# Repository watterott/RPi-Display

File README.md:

# RPi-Display
2.8" TFT-Display (320x240) with Touchpanel for all Raspberry Pi Models.

* Open-Source and released under the [Creative Commons Attribution Share-Alike License](https://creativecommons.org/licenses/by-sa/4.0/).
* **[Documentation on learn.watterott.com](https://learn.watterott.com)**

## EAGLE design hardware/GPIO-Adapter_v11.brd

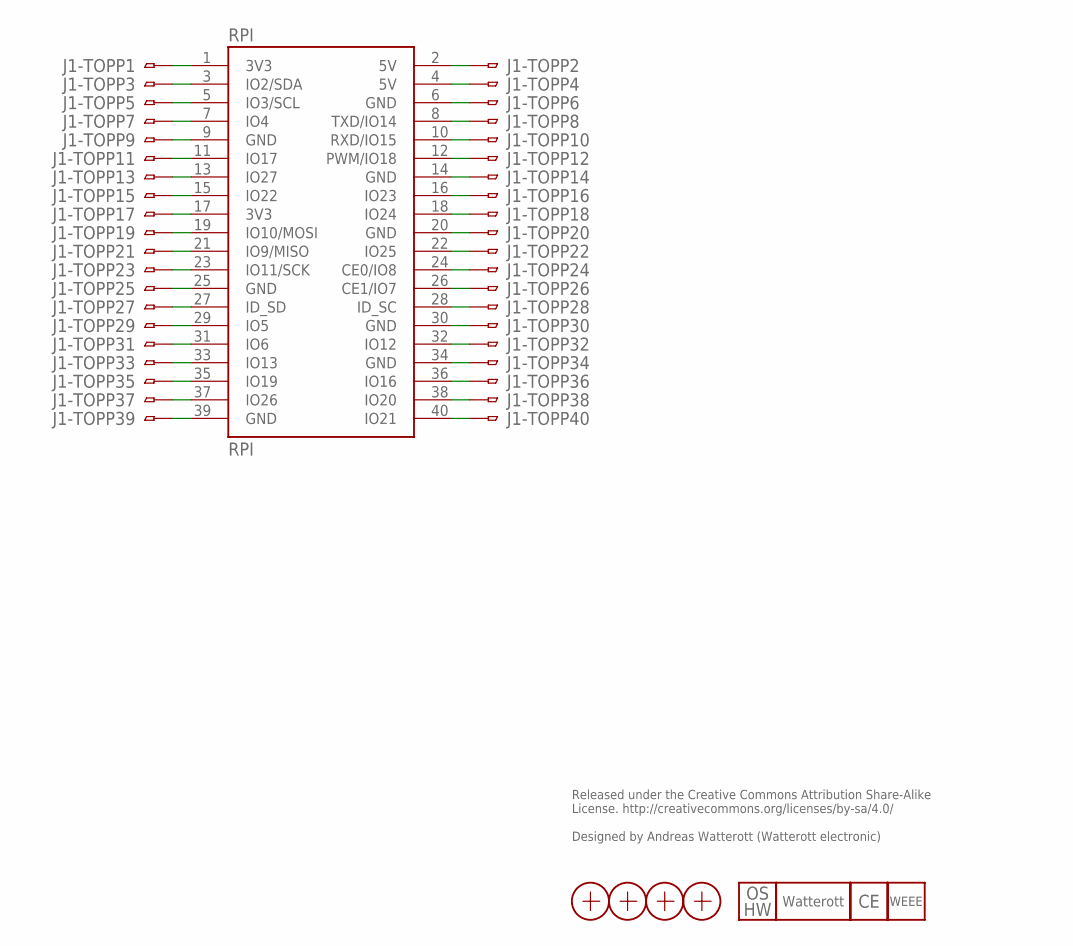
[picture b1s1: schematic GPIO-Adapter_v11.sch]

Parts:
J1-TOP: FPC40_PIN; FPC40-0.5
LOGO2: LOGO_OSHW-4; OSHW_4MM
LOGO3: LOGO_SPARK-4; SPARK_4MM
LOGO4: LOGO_CE-2; CE_2MM
LOGO5: LOGO_WEEE-4; WEEE_4MM
RPI: RPI; RPI-B+_CON_TOP
X1, X2, X3, X4: PASSER

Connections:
1: J1-TOP.1, RPI.1 (3V3)
2: J1-TOP.2, RPI.2 (5V)
3: J1-TOP.3, RPI.3 (IO2/SDA)
4: J1-TOP.4, RPI.4 (5V)
5: J1-TOP.5, RPI.5 (IO3/SCL)
6: J1-TOP.6, RPI.6 (GND)
7: J1-TOP.7, RPI.7 (IO4)
8: J1-TOP.8, RPI.8 (TXD/IO14)
9: J1-TOP.9, RPI.9 (GND)
10: J1-TOP.10, RPI.10 (RXD/IO15)
11: J1-TOP.11, RPI.11 (IO17)
12: J1-TOP.12, RPI.12 (PWM/IO18)
13: J1-TOP.13, RPI.13 (IO27)
14: J1-TOP.14, RPI.14 (GND)
15: J1-TOP.15, RPI.15 (IO22)
16: J1-TOP.16, RPI.16 (IO23)
17: J1-TOP.17, RPI.17 (3V3)
18: J1-TOP.18, RPI.18 (IO24)
19: J1-TOP.19, RPI.19 (IO10/MOSI)
20: J1-TOP.20, RPI.20 (GND)
21: J1-TOP.21, RPI.21 (IO9/MISO)
22: J1-TOP.22, RPI.22 (IO25)
23: J1-TOP.23, RPI.23 (IO11/SCK)
24: J1-TOP.24, RPI.24 (CE0/IO8)
25: J1-TOP.25, RPI.25 (GND)
26: J1-TOP.26, RPI.26 (CE1/IO7)
27: J1-TOP.27, RPI.27 (ID_SD)
28: J1-TOP.28, RPI.28 (ID_SC)
29: J1-TOP.29, RPI.29 (IO5)
30: J1-TOP.30, RPI.30 (GND)
31: J1-TOP.31, RPI.31 (IO6)
32: J1-TOP.32, RPI.32 (IO12)
33: J1-TOP.33, RPI.33 (IO13)
34: J1-TOP.34, RPI.34 (GND)
35: J1-TOP.35, RPI.35 (IO19)
36: J1-TOP.36, RPI.36 (IO16)
37: J1-TOP.37, RPI.37 (IO26)
38: J1-TOP.38, RPI.38 (IO20)
39: J1-TOP.39, RPI.39 (GND)
40: J1-TOP.40, RPI.40 (IO21)

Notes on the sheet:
Released under the Creative Commons Attribution Share-Alike License. http://creativecommons.org/licenses/by-sa/4.0/ Designed by Andreas Watterott (Watterott electronic)

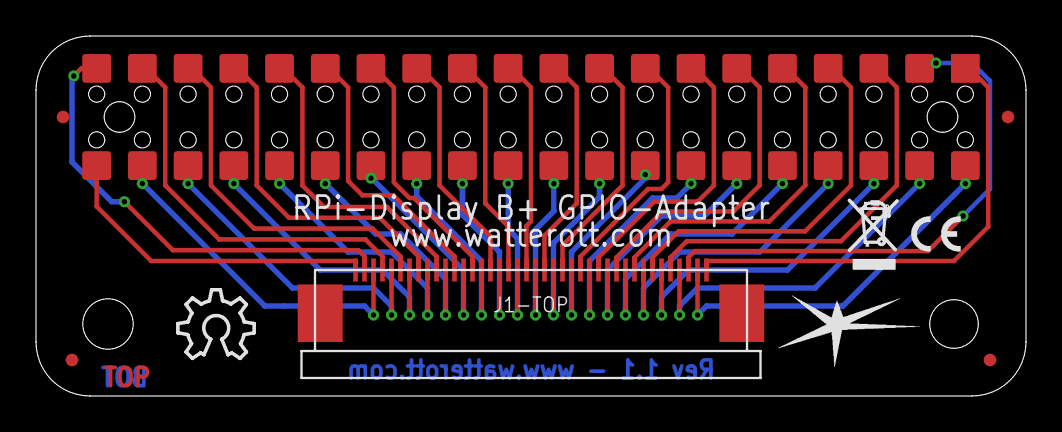
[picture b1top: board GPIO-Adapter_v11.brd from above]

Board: 2 copper layers, 55.0 x 20.0 mm, 10 parts (0 on the bottom side), 40 nets.

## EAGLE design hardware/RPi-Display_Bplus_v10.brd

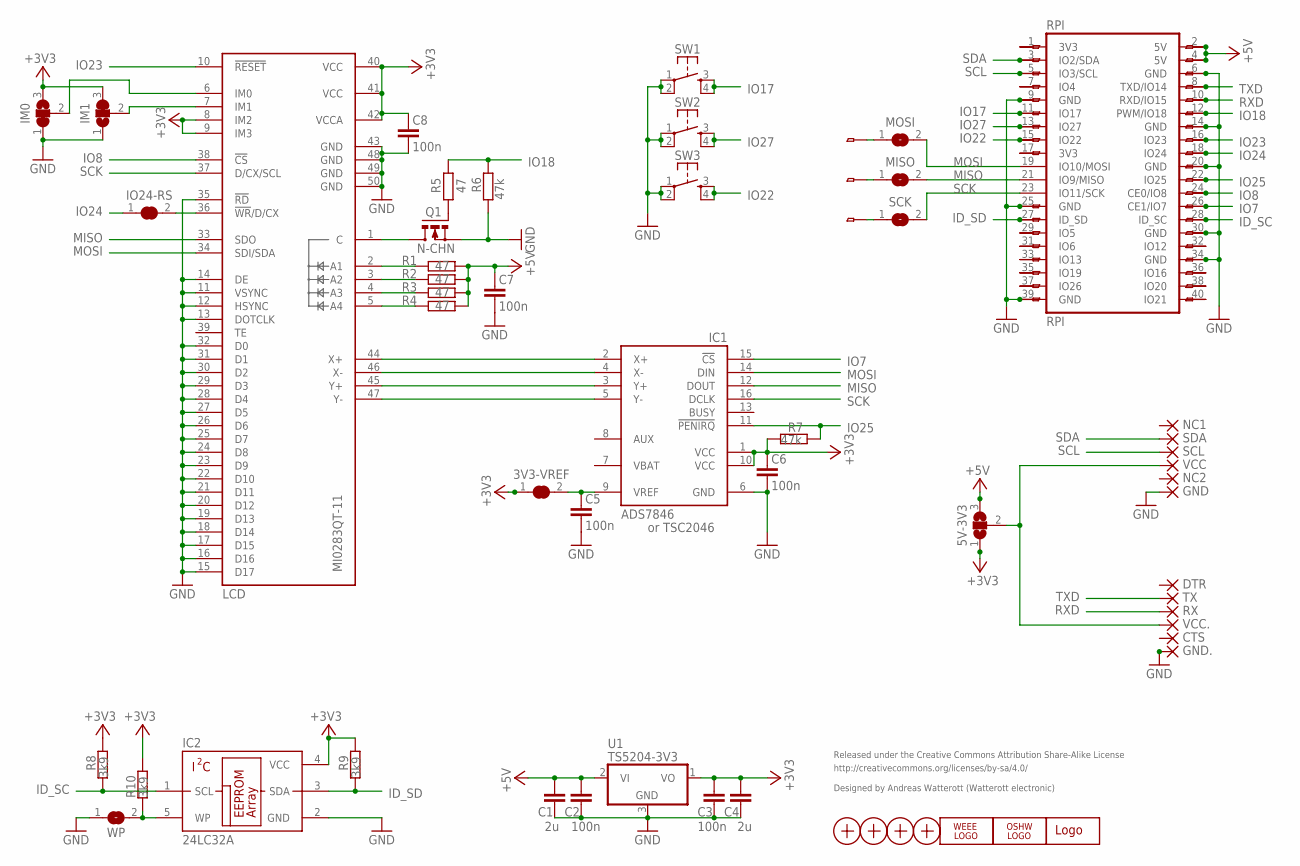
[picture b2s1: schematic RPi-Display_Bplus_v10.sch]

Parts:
3V3-VREF: JUMPER2-NOCREAM; JUMPER2_NC
5V-3V3: JUMPER3-NOCREAM; JUMPER3_NC
C1, C4: 2u; C0603
C2, C3, C5, C6, C7, C8: 100n; C0603
CTS: PAD-1.27-NC; PAD-1.27X2.54_NC
DTR: PAD-1.27-NC; PAD-1.27X2.54_NC
GND, GND.: PAD-1.27-NC; PAD-1.27X2.54_NC
GPIO: FH12-40S-0.5SH
IC1: ADS7846; SSOP16
IC2: 24LC32A; SOT23-5
IM0, IM1: JUMPER3-NOCREAM; JUMPER3_NC
IO24-RS: JUMPER2-NOCREAM; JUMPER2_NC
LCD: MI0283QT-11; MI0283QT11
LOGO1: OSHW_LOGO_6MILX0150-NT; OSHW_6X150_NOTEXT
LOGO2: WEEE_LOGO; WEEE
MISO: JUMPER2-NOCREAM; JUMPER2_NC
MOSI: JUMPER2-NOCREAM; JUMPER2_NC
NC1, NC2: PAD-1.27-NC; PAD-1.27X2.54_NC
Q1: N-CHN; MICRO3
R1, R2, R3, R4, R5: 47; R0603
R6, R7: 47k; R0603
R8, R9, R10: 3k9; R0603
RPI: RPI; RPI_B+
RX: PAD-1.27-NC; PAD-1.27X2.54_NC
SCK: JUMPER2-NOCREAM; JUMPER2_NC
SCL: PAD-1.27-NC; PAD-1.27X2.54_NC
SDA: PAD-1.27-NC; PAD-1.27X2.54_NC
SW1, SW2, SW3: SWITCH-PTS840P; SW_PTS840P
TX: PAD-1.27-NC; PAD-1.27X2.54_NC
U1: TS5204-3V3; SOT23
U$1: WE-LOGO
VCC, VCC.: PAD-1.27-NC; PAD-1.27X2.54_NC
WP: JUMPER2-NOCREAM; JUMPER2_NC
X1, X2, X3, X4: PASSER

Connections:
+3V3: 3V3-VREF.1, 5V-3V3.1, C3.1, C4.1, C6.1, C8.1, IC1.1 (VCC), IC1.10 (VCC), IC2.4 (VCC), IM0.3, IM1.3, LCD.8 (IM2), LCD.9 (IM3), LCD.40 (VCC), LCD.41 (VCC), LCD.42 (VCCA), R7.2, R8.1, R9.1, R10.1, U1.1 (VO)
+5V: 5V-3V3.3, C1.1, C2.1, C7.1, GPIO.37, GPIO.39, R1.2, R2.2, R3.2, R4.2, RPI.2 (5V), RPI.4 (5V), U1.2 (VI)
C1: LCD.1 (C), Q1.3 (D)
GND: C1.2, C2.2, C3.2, C4.2, C5.2, C6.2, C7.2, C8.2, GND.1, GND..1, GPIO.2, GPIO.7, GPIO.11, GPIO.16, GPIO.21, GPIO.27, GPIO.32, GPIO.35, IC1.6 (GND), IC2.2 (GND), IM0.1, IM1.1, LCD.11 (VSYNC), LCD.12 (HSYNC), LCD.13 (DOTCLK), LCD.14 (DE), LCD.15 (D17), LCD.16 (D16), LCD.17 (D15), LCD.18 (D14), LCD.19 (D13), LCD.20 (D12), LCD.21 (D11), LCD.22 (D10), LCD.23 (D9), LCD.24 (D8), LCD.25 (D7), LCD.26 (D6), LCD.27 (D5), LCD.28 (D4), LCD.29 (D3), LCD.30 (D2), LCD.31 (D1), LCD.32 (D0), LCD.35 (!RD), LCD.43 (GND), LCD.48 (GND), LCD.49 (GND), LCD.50 (GND), Q1.2 (S), R6.2, RPI.6 (GND), RPI.9 (GND), RPI.14 (GND), RPI.20 (GND), RPI.25 (GND), RPI.30 (GND), RPI.34 (GND), RPI.39 (GND), SW1.1, SW1.2 (P1), SW2.1, SW2.2 (P1), SW3.1, SW3.2 (P1), U1.3 (GND), WP.1
ID_SC: GPIO.13, IC2.1 (SCL), R8.2, RPI.28 (ID_SC)
ID_SD: GPIO.14, IC2.3 (SDA), R9.2, RPI.27 (ID_SD)
IM0: IM0.2, LCD.6 (IM0)
IM1: IM1.2, LCD.7 (IM1)
IO7: GPIO.15, IC1.15 (!CS), RPI.26 (CE1/IO7)
IO8: GPIO.17, LCD.38 (!CS), RPI.24 (CE0/IO8)
IO17: GPIO.30, RPI.11 (IO17), SW1.3 (S), SW1.4 (S1)
IO18: GPIO.29, R5.2, R6.1, RPI.12 (PWM/IO18)
IO22: GPIO.26, RPI.15 (IO22), SW3.3 (S), SW3.4 (S1)
IO23: GPIO.25, LCD.10 (!RESET), RPI.16 (IO23)
IO24: GPIO.23, IO24-RS.1, RPI.18 (IO24)
IO25: GPIO.19, IC1.11 (!PENIRQ), R7.1, RPI.22 (IO25)
IO27: GPIO.28, RPI.13 (IO27), SW2.3 (S), SW2.4 (S1)
LEDPWM: Q1.1 (G), R5.1
LED_A1: LCD.2 (A1), R1.1
LED_A2: LCD.3 (A2), R2.1
LED_A3: LCD.4 (A3), R3.1
LED_A4: LCD.5 (A4), R4.1
MISO: IC1.12 (DOUT), LCD.33 (SDO), MISO.2, RPI.21 (IO9/MISO)
MOSI: IC1.14 (DIN), LCD.34 (SDI/SDA), MOSI.2, RPI.19 (IO10/MOSI)
unnamed: IO24-RS.2, LCD.36 (!WR!/D/CX)
unnamed: IC2.5 (WP), R10.2, WP.2
unnamed: GPIO.22, MOSI.1
unnamed: 5V-3V3.2, VCC.1, VCC..1
unnamed: GPIO.20, MISO.1
unnamed: GPIO.18, SCK.1
unnamed: GPIO.40, RPI.1 (3V3)
unnamed: GPIO.34, RPI.7 (IO4)
unnamed: GPIO.24, RPI.17 (3V3)
unnamed: GPIO.12, RPI.29 (IO5)
unnamed: GPIO.10, RPI.31 (IO6)
unnamed: GPIO.8, RPI.33 (IO13)
unnamed: GPIO.6, RPI.35 (IO19)
unnamed: GPIO.4, RPI.37 (IO26)
unnamed: GPIO.9, RPI.32 (IO12)
unnamed: GPIO.5, RPI.36 (IO16)
unnamed: GPIO.3, RPI.38 (IO20)
unnamed: GPIO.1, RPI.40 (IO21)
RXD: GPIO.31, RPI.10 (RXD/IO15), RX.1
SCK: IC1.16 (DCLK), LCD.37 (D/CX/SCL), RPI.23 (IO11/SCK), SCK.2
SCL: GPIO.36, RPI.5 (IO3/SCL), SCL.1
SDA: GPIO.38, RPI.3 (IO2/SDA), SDA.1
TXD: GPIO.33, RPI.8 (TXD/IO14), TX.1
VREF: 3V3-VREF.2, C5.1, IC1.9 (VREF)
X+: IC1.2 (X+), LCD.44 (X+)
X-: IC1.4 (X-), LCD.46 (X-)
Y+: IC1.3 (Y+), LCD.45 (Y+)
Y-: IC1.5 (Y-), LCD.47 (Y-)

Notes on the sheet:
Released under the Creative Commons Attribution Share-Alike License
http://creativecommons.org/licenses/by-sa/4.0/
Designed by Andreas Watterott (Watterott electronic)
or TSC2046

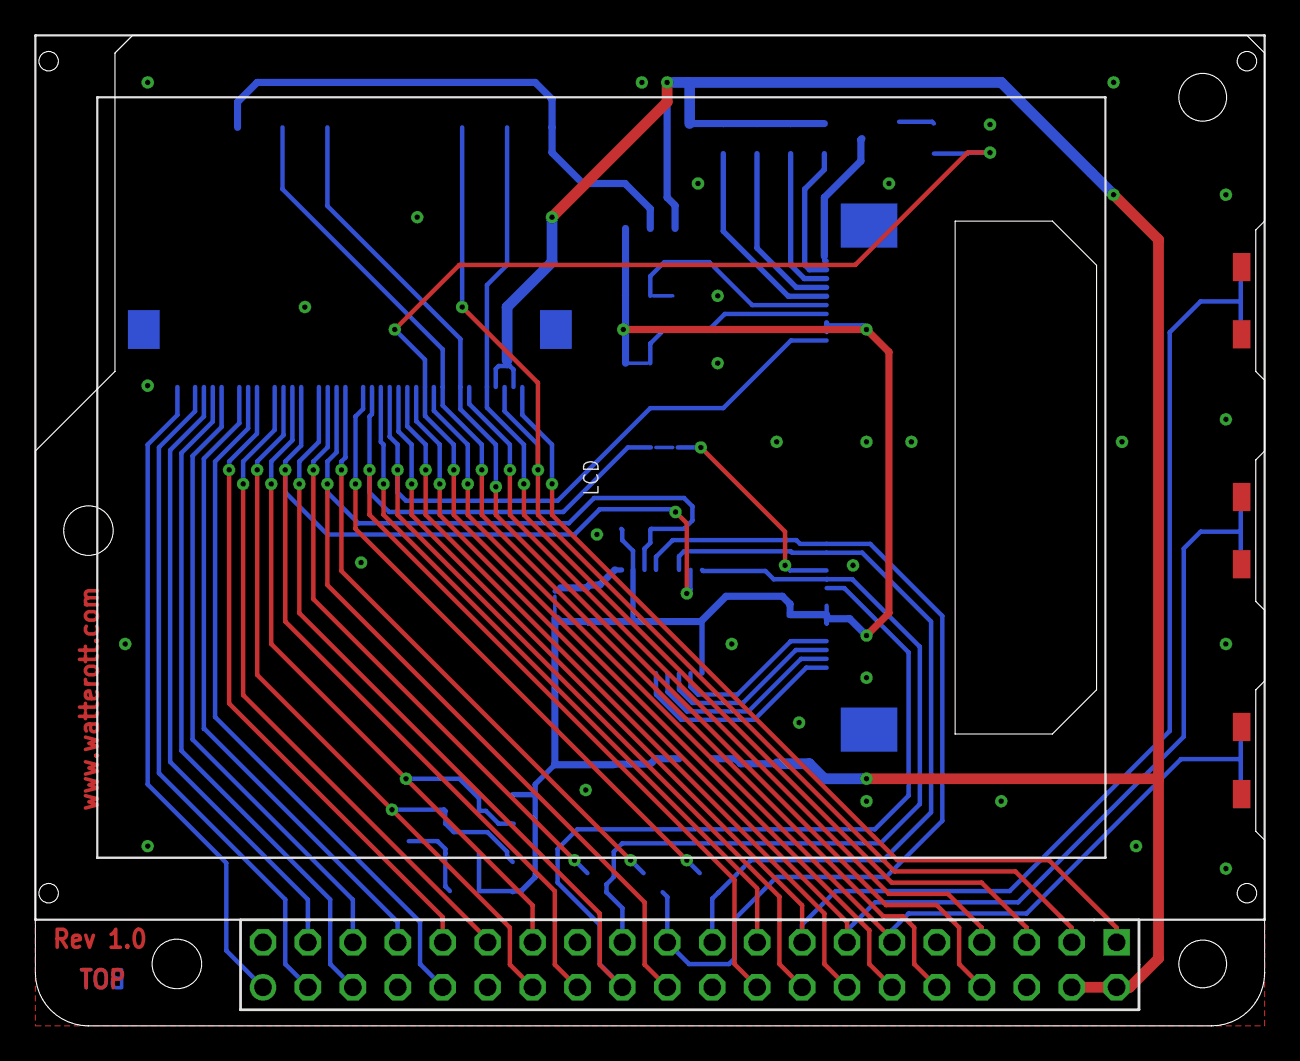
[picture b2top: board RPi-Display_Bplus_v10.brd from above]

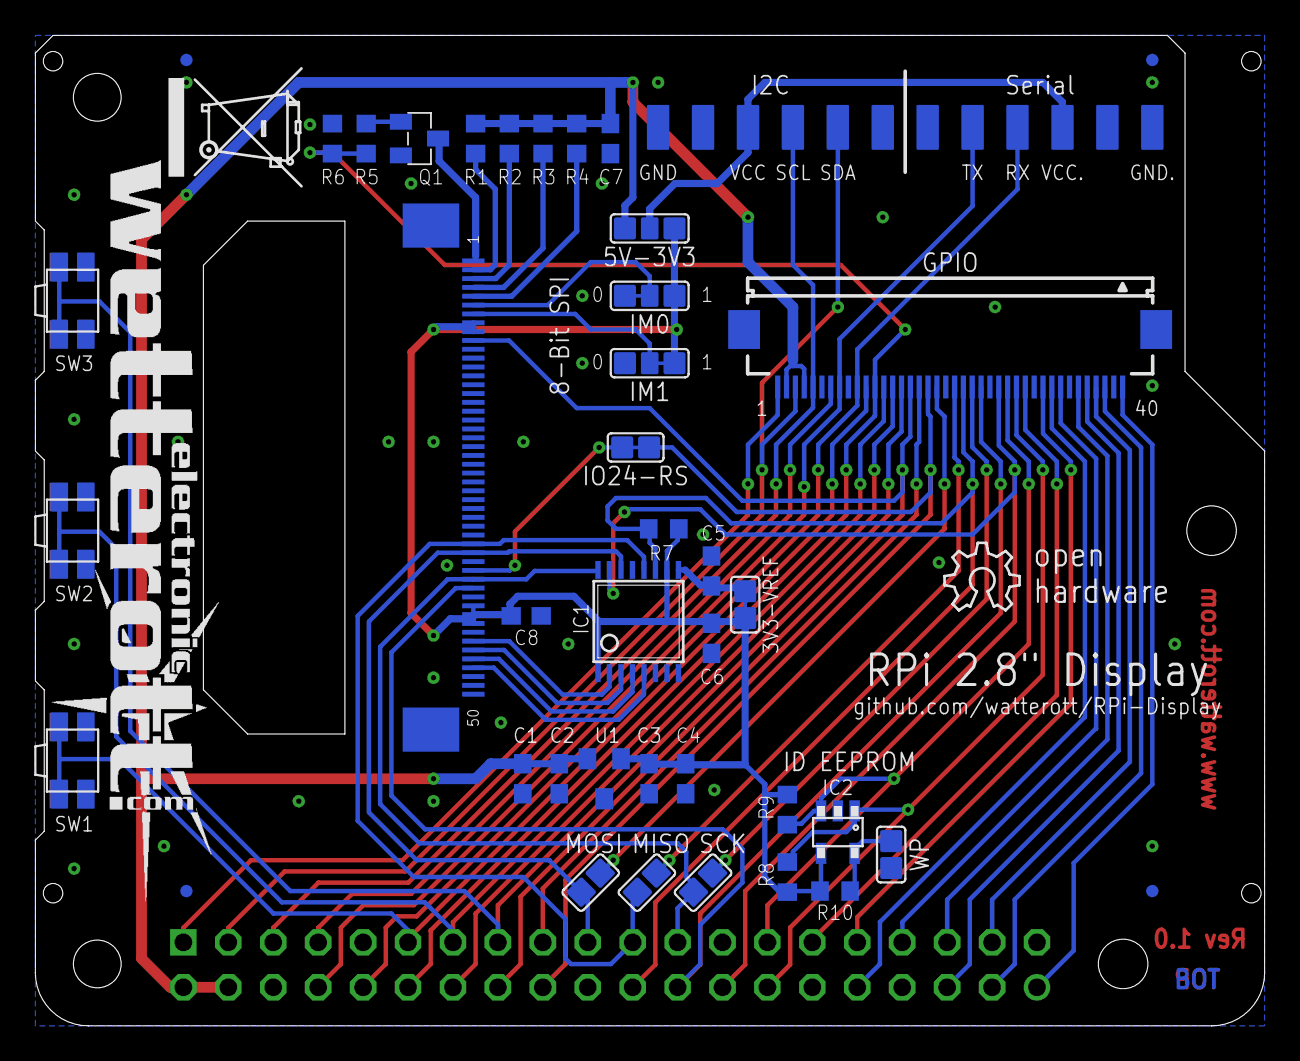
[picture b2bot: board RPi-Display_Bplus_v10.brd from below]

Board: 2 copper layers, 69.5 x 56.0 mm, 56 parts (54 on the bottom side), 52 nets.

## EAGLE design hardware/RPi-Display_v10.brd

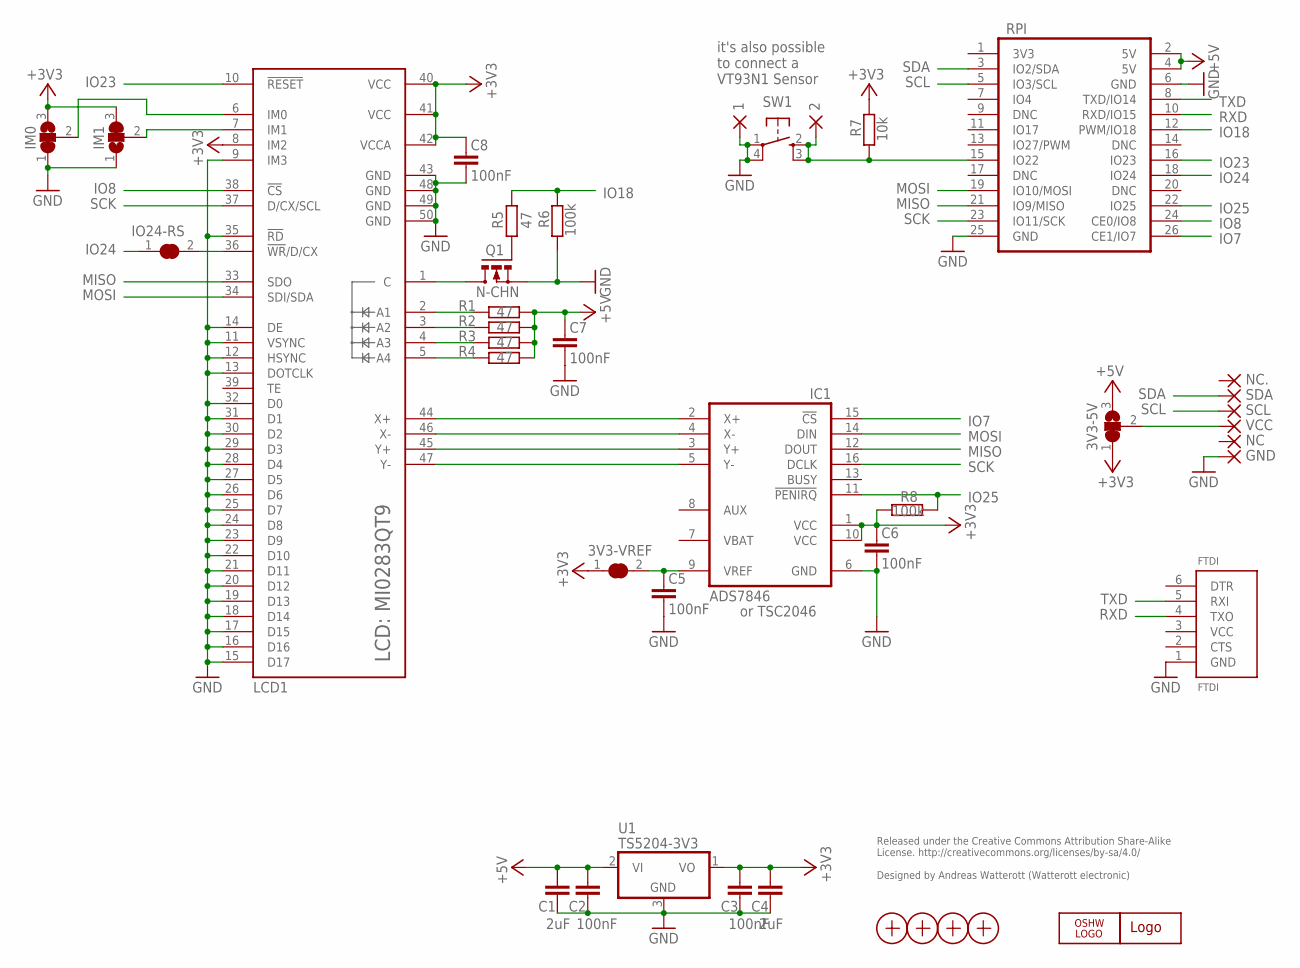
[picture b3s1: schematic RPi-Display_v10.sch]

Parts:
1, 2: WIREPADSMD1,27-254; SMD1,27-2,54
3V3-5V: SJ2W; SJ_2
3V3-VREF: SJ
C1, C4: 2uF; C0603
C2, C3, C5, C6, C7, C8: 100nF; C0603
FTDI: FTDI
GND: WIREPADSMD1,27-254; SMD1,27-2,54
IC1: ADS7846; SSOP16
IM0, IM1: SJ2W; SJ_2
IO24-RS: SJ
LCD1: MI0283QT9
LOGO1: OSHW_LOGO_6MILX0150-NT; OSHW_6X150_NOTEXT
NC, NC.: WIREPADSMD1,27-254; SMD1,27-2,54
Q1: N-CHN; MICRO3
R1, R2, R3, R4, R5: 47; R0603
R6, R8: 100k; R0603
R7: 10k; R0603
RPI: RPI
SCL: WIREPADSMD1,27-254; SMD1,27-2,54
SDA: WIREPADSMD1,27-254; SMD1,27-2,54
SW1: SW4S; SW_SMD4
U1: TS5204-3V3; SOT23
U$1: WE-LOGO
VCC: WIREPADSMD1,27-254; SMD1,27-2,54
X1, X2, X3, X4: PASSER

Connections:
+3V3: 3V3-5V.1, 3V3-VREF.1, C3.1, C4.1, C6.1, C8.1, IC1.1 (VCC), IC1.10 (VCC), IM0.3, IM1.3, LCD1.8 (IM2), LCD1.40 (VCC), LCD1.41 (VCC), LCD1.42 (VCCA), R7.1, R8.2, U1.1 (VO)
+5V: 3V3-5V.3, C1.1, C2.1, C7.1, R1.2, R2.2, R3.2, R4.2, RPI.2 (5V), RPI.4 (5V), U1.2 (VI)
C1: LCD1.1 (C), Q1.3 (D)
GND: 1.1, C1.2, C2.2, C3.2, C4.2, C5.2, C6.2, C7.2, C8.2, FTDI.1 (GND), GND.1, IC1.6 (GND), IM0.1, IM1.1, LCD1.9 (IM3), LCD1.11 (VSYNC), LCD1.12 (HSYNC), LCD1.13 (DOTCLK), LCD1.14 (DE), LCD1.15 (D17), LCD1.16 (D16), LCD1.17 (D15), LCD1.18 (D14), LCD1.19 (D13), LCD1.20 (D12), LCD1.21 (D11), LCD1.22 (D10), LCD1.23 (D9), LCD1.24 (D8), LCD1.25 (D7), LCD1.26 (D6), LCD1.27 (D5), LCD1.28 (D4), LCD1.29 (D3), LCD1.30 (D2), LCD1.31 (D1), LCD1.32 (D0), LCD1.35 (!RD), LCD1.43 (GND), LCD1.48 (GND), LCD1.49 (GND), LCD1.50 (GND), Q1.2 (S), R6.2, RPI.6 (GND), RPI.25 (GND), SW1.1, SW1.4 (P1), U1.3 (GND)
IM0: IM0.2, LCD1.6 (IM0)
IM1: IM1.2, LCD1.7 (IM1)
IO7: IC1.15 (!CS), RPI.26 (CE1/IO7)
IO8: LCD1.38 (!CS), RPI.24 (CE0/IO8)
IO18: R5.2, R6.1, RPI.12 (PWM/IO18)
IO22: 2.1, R7.2, RPI.15 (IO22), SW1.2 (S), SW1.3 (S1)
IO23: LCD1.10 (!RESET), RPI.16 (IO23)
IO24: IO24-RS.1, RPI.18 (IO24)
IO25: IC1.11 (!PENIRQ), R8.1, RPI.22 (IO25)
LEDPWM: Q1.1 (G), R5.1
LED_A1: LCD1.2 (A1), R1.1
LED_A2: LCD1.3 (A2), R2.1
LED_A3: LCD1.4 (A3), R3.1
LED_A4: LCD1.5 (A4), R4.1
MISO: IC1.12 (DOUT), LCD1.33 (SDO), RPI.21 (IO9/MISO)
MOSI: IC1.14 (DIN), LCD1.34 (SDI/SDA), RPI.19 (IO10/MOSI)
unnamed: IO24-RS.2, LCD1.36 (!WR!/D/CX)
unnamed: 3V3-5V.2, VCC.1
RXD: FTDI.4 (TXO), RPI.10 (RXD/IO15)
SCK: IC1.16 (DCLK), LCD1.37 (D/CX/SCL), RPI.23 (IO11/SCK)
SCL: RPI.5 (IO3/SCL), SCL.1
SDA: RPI.3 (IO2/SDA), SDA.1
TXD: FTDI.5 (RXI), RPI.8 (TXD/IO14)
VREF: 3V3-VREF.2, C5.1, IC1.9 (VREF)
X+: IC1.2 (X+), LCD1.44 (X+)
X-: IC1.4 (X-), LCD1.46 (X-)
Y+: IC1.3 (Y+), LCD1.45 (Y+)
Y-: IC1.5 (Y-), LCD1.47 (Y-)

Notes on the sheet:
Released under the Creative Commons Attribution Share-Alike License. http://creativecommons.org/licenses/by-sa/4.0/ Designed by Andreas Watterott (Watterott electronic)
or TSC2046
it's also possible to connect a VT93N1 Sensor

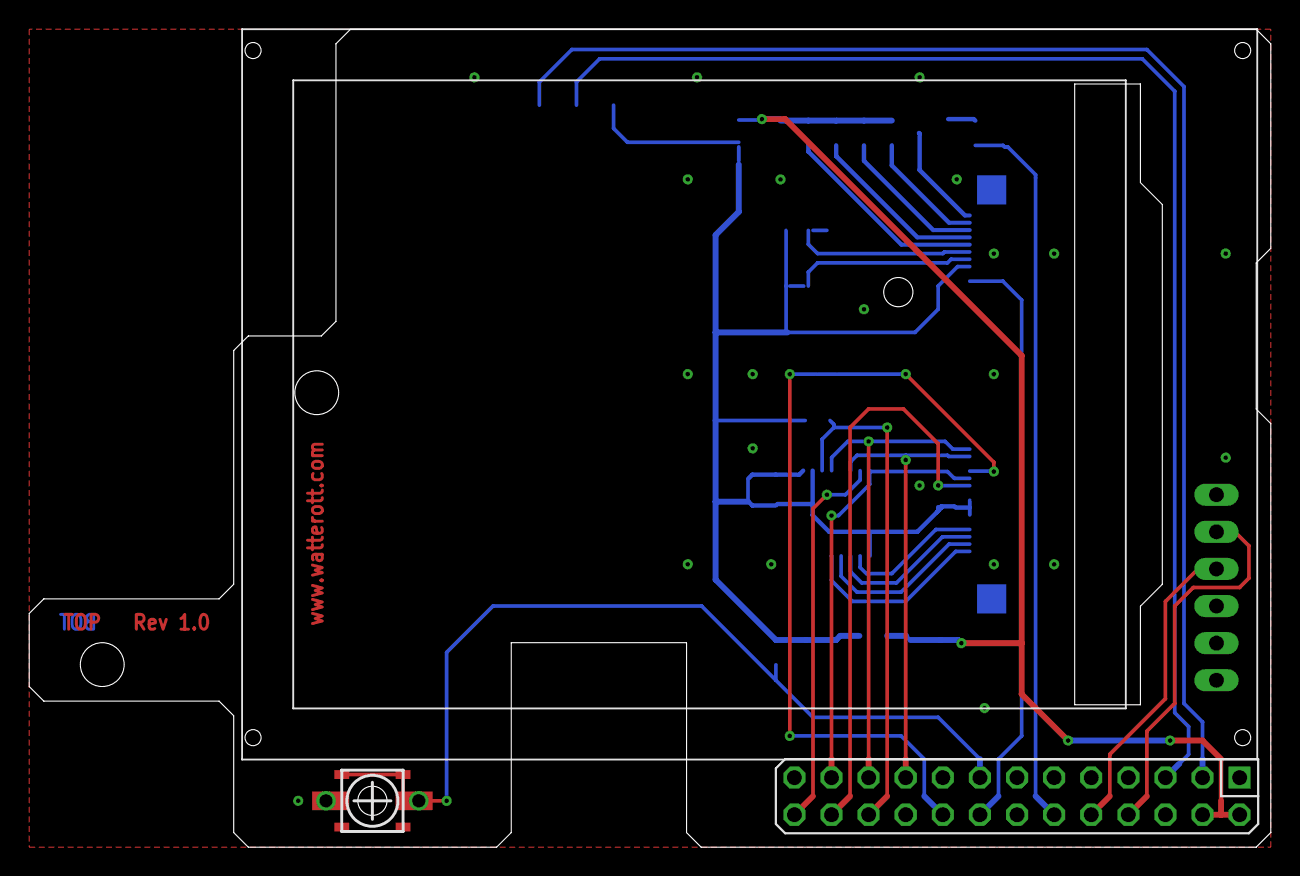
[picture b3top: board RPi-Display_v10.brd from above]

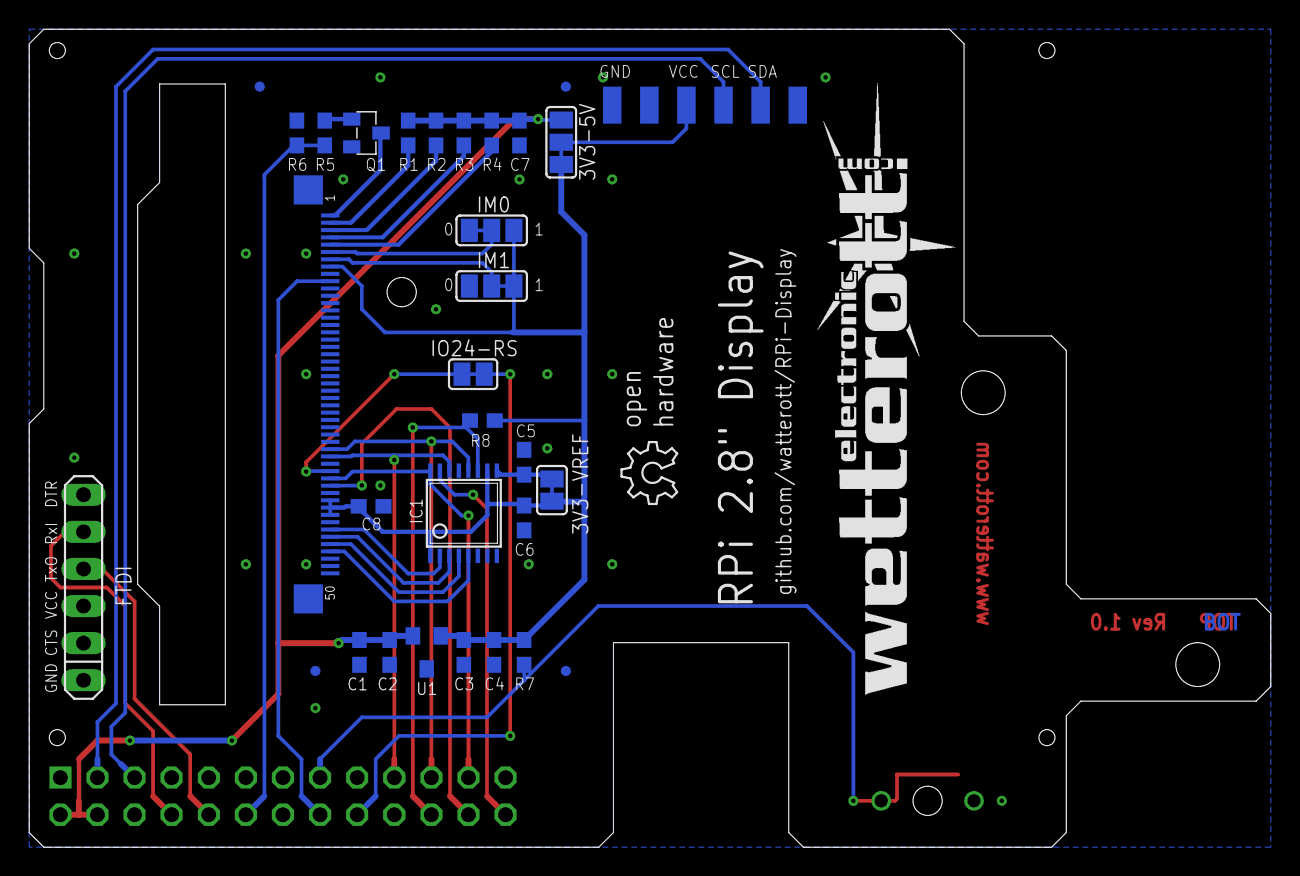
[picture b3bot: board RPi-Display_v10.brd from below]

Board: 2 copper layers, 85.0 x 56.0 mm, 42 parts (37 on the bottom side), 32 nets.

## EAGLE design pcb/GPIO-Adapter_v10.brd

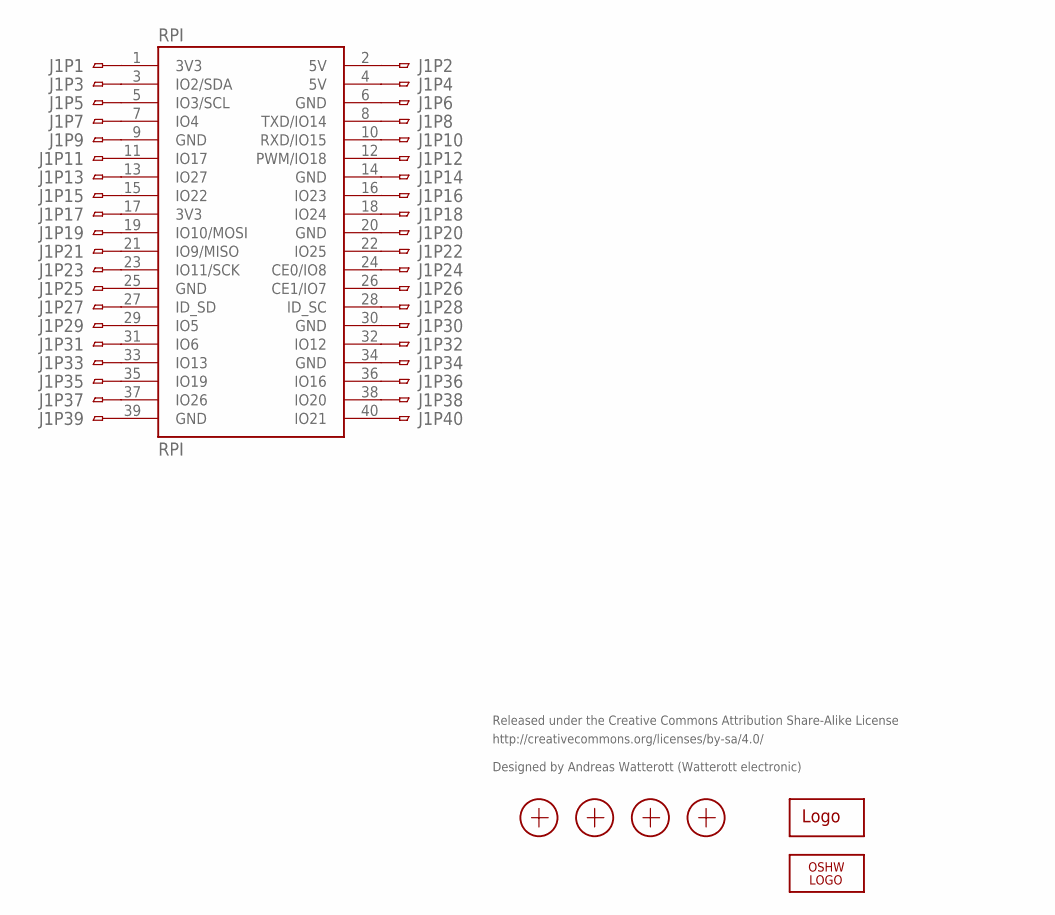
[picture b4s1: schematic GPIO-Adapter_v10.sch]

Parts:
J1: FPC40_PIN; FPC40
LOGO1: OSHW_LOGO_6MILX0150-NT; OSHW_6X150_NOTEXT
LOGO2: LOGO-S_PLACE_M; SPARK_TPLACE_M
RPI: RPI; RPI-B+_CON
X1, X2, X3, X4: PASSER

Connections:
unnamed: J1.40, RPI.40 (IO21)
unnamed: J1.2, RPI.2 (5V)
unnamed: J1.3, RPI.3 (IO2/SDA)
unnamed: J1.4, RPI.4 (5V)
unnamed: J1.6, RPI.6 (GND)
unnamed: J1.5, RPI.5 (IO3/SCL)
unnamed: J1.7, RPI.7 (IO4)
unnamed: J1.8, RPI.8 (TXD/IO14)
unnamed: J1.9, RPI.9 (GND)
unnamed: J1.10, RPI.10 (RXD/IO15)
unnamed: J1.11, RPI.11 (IO17)
unnamed: J1.12, RPI.12 (PWM/IO18)
unnamed: J1.13, RPI.13 (IO27)
unnamed: J1.14, RPI.14 (GND)
unnamed: J1.15, RPI.15 (IO22)
unnamed: J1.16, RPI.16 (IO23)
unnamed: J1.17, RPI.17 (3V3)
unnamed: J1.18, RPI.18 (IO24)
unnamed: J1.19, RPI.19 (IO10/MOSI)
unnamed: J1.20, RPI.20 (GND)
unnamed: J1.21, RPI.21 (IO9/MISO)
unnamed: J1.22, RPI.22 (IO25)
unnamed: J1.23, RPI.23 (IO11/SCK)
unnamed: J1.24, RPI.24 (CE0/IO8)
unnamed: J1.25, RPI.25 (GND)
unnamed: J1.26, RPI.26 (CE1/IO7)
unnamed: J1.27, RPI.27 (ID_SD)
unnamed: J1.28, RPI.28 (ID_SC)
unnamed: J1.29, RPI.29 (IO5)
unnamed: J1.30, RPI.30 (GND)
unnamed: J1.31, RPI.31 (IO6)
unnamed: J1.32, RPI.32 (IO12)
unnamed: J1.33, RPI.33 (IO13)
unnamed: J1.34, RPI.34 (GND)
unnamed: J1.35, RPI.35 (IO19)
unnamed: J1.36, RPI.36 (IO16)
unnamed: J1.37, RPI.37 (IO26)
unnamed: J1.38, RPI.38 (IO20)
unnamed: J1.1, RPI.1 (3V3)
unnamed: J1.39, RPI.39 (GND)

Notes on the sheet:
Released under the Creative Commons Attribution Share-Alike License
http://creativecommons.org/licenses/by-sa/4.0/
Designed by Andreas Watterott (Watterott electronic)

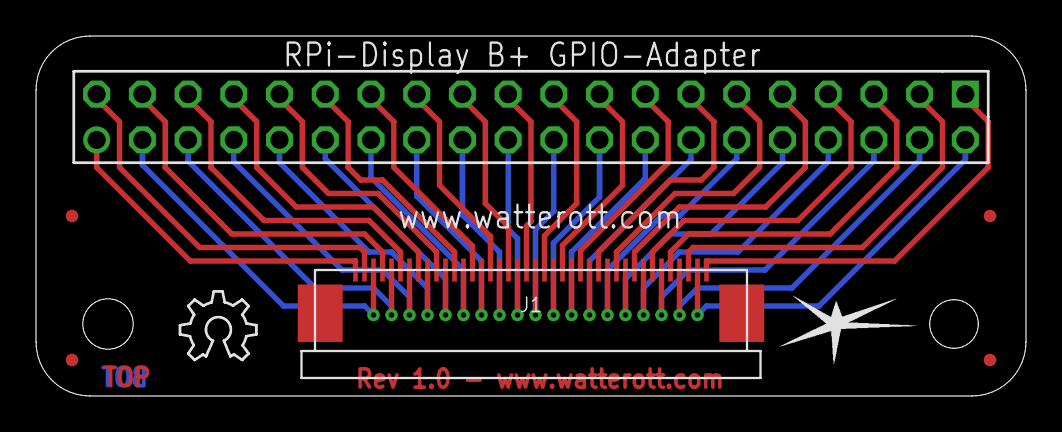
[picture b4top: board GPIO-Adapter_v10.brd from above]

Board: 2 copper layers, 55.0 x 20.0 mm, 8 parts (0 on the bottom side), 40 nets.

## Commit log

2013-12-24 added image
2013-12-24 added schematics and layout
2014-03-10 updated license infos
2014-03-21 added cmdline.txt
2014-05-15 added cmdline.txt for RPi-ShieldBridge
2014-06-25 Revert "updated readme"
    This reverts commit 691a2a8a996f74ae081c52097394c80c3b1aa710.
2014-06-25 Revert "Revert "updated readme""
    This reverts commit 4a701f2da51f89bf0852589f6d1ab9af30128c3e.
2014-07-13 updated readme and docu
2014-07-14 updated docu
2014-08-15 updated schematic and layout files
2014-08-21 updated layout and schematics
2014-08-21 updated image
2014-08-24 added EEPROM config
2014-09-24 updated docu and readme
2014-10-23 added backlight dimming tool
2014-11-06 cleaned up schematics and layout
2014-11-07 added GPIO-Adapter
2014-11-17 updated dou
2014-12-10 updated schematics
2015-01-05 added projects
2015-01-11 moved image
2015-01-22 updated layout
2015-01-22 updated projects
2015-02-08 updated docu for Device Tree enabled Kernel
2015-02-13 Change /dev/input/eventX device char to touchscreen
    Create a new udrev-rule for making a symlink from the current touchscreen device char /dev/input/eventX to /dev/input/touchscreen
2015-02-13 Updated calibration instruction
    ts_calibrate: changed parameter /dev/input/eventX to /dev/input/touchscreen
2015-02-14 Revert "updated docu"
    This reverts commit c5df3be00804876e27721cce14bf0da0b5744f92.
2015-03-09 updated doxu
2015-03-12 added PiMenu to the list of projects
2015-03-15 added installation script
2015-03-15 updated installation script
2015-03-15 removed apt-get upgrade
2015-03-16 added check for device tree
2015-03-30 added rev 1.1 layout and schematics
2015-04-22 added check for rpi-update
2015-04-22 added support for other Linux systems
2015-06-08 added fbcp service script
2015-07-02 improved OS support
2015-08-18 added additional infos
2015-08-21 changed path structure
2015-11-26 updated docu and schematics
2015-11-29 Updates how to use pygame with the display
    Include information how to use pygame with the display. The Jessie image won't work correctly with the input of the touchscreen, whereas the display works without any problems. Additionally include l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
    Greetings from Austria!
2015-12-11 console blanking workaround for jessie
2016-01-20 added dual screen mode
2016-01-22 updated dual screen mode settings
2017-03-28 added TransformationMatrix
2017-03-28 updated calibration script
2017-07-30 moved docu to docs
2017-12-28 add backlight pin override
    add backlight pin override
2018-01-30 moved files
2018-09-27 added GPIO-Adapter rev 1.1
2018-09-28 typo fix
2018-12-13 moved to FFC-Extender repo
2018-12-29 update fbcp service path accordingly
2019-03-23 added backlight example
2019-05-24 updated script
2019-11-29 added Pygame example
2020-05-12 changed file name
2020-05-16 added license info
2020-08-17 fix for rpi-5.4
2020-08-17 added compiled overlay for rpi-5.4
2022-01-22 rename file
2022-01-22 overlay fix for kernel 5.10+
